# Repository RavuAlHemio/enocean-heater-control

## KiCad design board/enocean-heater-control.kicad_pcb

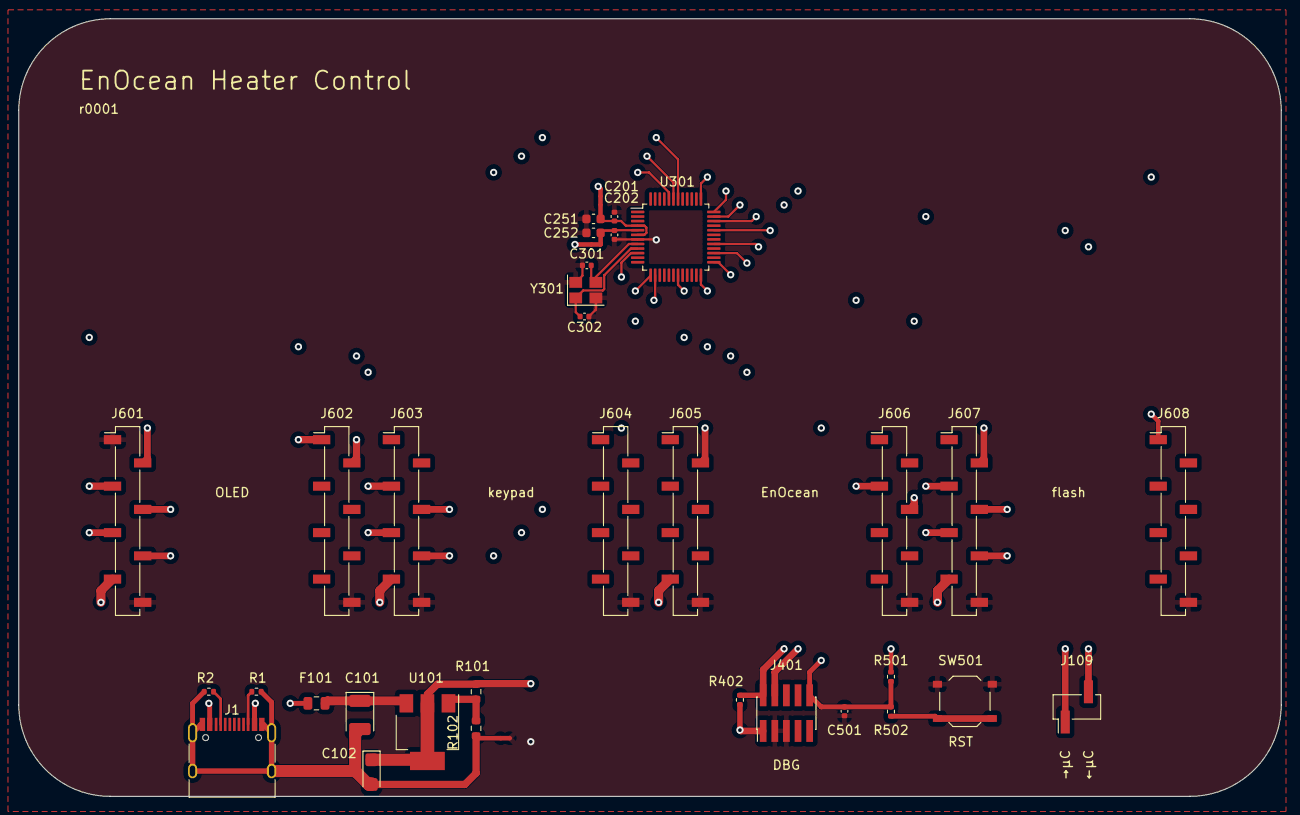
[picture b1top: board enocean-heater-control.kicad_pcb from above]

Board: 4 copper layers, 138.0 x 85.0 mm, 35 parts (0 on the bottom side), 29 nets.

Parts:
C101: 100µF; CP_EIA-3528-21_Kemet-B
C102: 10µF; CP_EIA-3216-18_Kemet-A
C201, C202, C501: 100nF; C_0402_1005Metric
C251: 4.7µF; C_0603_1608Metric
C252: 1µF; C_0603_1608Metric
C301, C302: 20pF; C_0402_1005Metric
F101: 500mA; Fuse_0805_2012Metric
J1: USB_C_Receptacle_PowerOnly_6P; USB_C_Receptacle_HRO_TYPE-C-31-M-12
J109: Conn_01x02; PinHeader_1x02_P2.54mm_Vertical_SMD_Pin1Left
J401: DBG; PinHeader_2x05_P1.27mm_Vertical_SMD
J601, J602, J603, J604, J605, J606, J607, J608: Conn_01x08; PinSocket_1x08_P2.54mm_Vertical_SMD_Pin1Left
NT101, NT201, NT202: NetTie_2; NetTie-2_SMD_Pad0.5mm
R1, R2: 5.1kΩ; R_0402_1005Metric
R101: 330Ω; R_0603_1608Metric
R102: 560Ω; R_0603_1608Metric
R402: 100kΩ; R_0402_1005Metric
R501: 2.2kΩ; R_0402_1005Metric
R502: 330Ω; R_0402_1005Metric
SW501: RST; SW_Push_1P1T_XKB_TS-1187A
U101: LM317AEMP; SOT-223-3_TabPin2
U301: STM32G0B0KETx; LQFP-48_7x7mm_P0.5mm
Y301: 16MHz; Crystal_SMD_3225-4Pin_3.2x2.5mm

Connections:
/+3.3V: C102.1, J401.1, J601.7, J603.7, J605.7, J607.7, NT201.2, NT202.1, R101.1, R402.1, R501.2, U101.2 (VO)
/CIPO: J601.5, J603.5, J607.5, U301.43 (PB4)
/COPI: J601.6, J603.6, J607.6, U301.44 (PB5)
/ENO_C2P: J606.4, U301.13 (PA2)
/ENO_P2C: J606.3, U301.14 (PA3)
/FLASH_~CS: J607.3, U301.34 (PA12/PA10)
/FLASH_~WP: J608.1, U301.37 (PA15)
/GND: C201.2, C202.2, C251.2, C252.2, C301.2, C302.1, C501.1, J401.3, J401.5, J601.1, J601.8, J602.8, J603.8, J604.8, J605.8, J606.8, J607.8, J608.8, NT101.2, SW501.1, U301.7 (VSS), Y301.2, Y301.4
/KPAD_~CS: J603.3, U301.27 (PB15)
/Microcontroller/Clock/MCU_OSC_IN: C301.1, U301.8 (PF0), Y301.3
/Microcontroller/Clock/MCU_OSC_OUT: C302.2, U301.9 (PF1), Y301.1
/Microcontroller/DBG_UART_MCURX: J109.1, U301.32 (PA10/NC)
/Microcontroller/DBG_UART_MCUTX: J109.2, U301.29 (PA9/NC)
/Microcontroller/Debug/SWCLK: J401.4, U301.36 (PA14)
/Microcontroller/Debug/SWDIO: J401.2, R402.2, U301.35 (PA13)
/Microcontroller/VDD: C201.1, C251.1, NT201.1, U301.4 (VBAT), U301.6 (VDD)
/Microcontroller/VREF+: C202.1, C252.1, NT202.2, U301.5 (VREF+)
/OLED_D_~C: J602.1, U301.24 (PB12)
/OLED_EN: J602.2, U301.25 (PB13)
/OLED_~CS: J601.3, U301.19 (PB0)
/Power Supply/GND_{USB}: C101.2, C102.2, J1.A1 (GND), J1.A12 (GND), J1.B1 (GND), J1.B12 (GND), J1.S1 (SHIELD), NT101.1, R1.2, R2.2, R102.2
/Power Supply/V_{USB}: F101.1, J1.A4 (VBUS), J1.A9 (VBUS), J1.B4 (VBUS), J1.B9 (VBUS)
/SCK: J601.4, J603.4, J607.4, U301.42 (PB3)
/~RST: C501.2, J401.10, J601.2, J605.2, J607.2, R501.1, R502.1, U301.10 (NRST)
unnamed: J1.A5 (CC1), R2.1
unnamed: J1.B5 (CC2), R1.1
unnamed: R502.2, SW501.2
unnamed: R101.2, R102.1, U101.1 (ADJ)
unnamed: C101.1, F101.2, U101.3 (VI)

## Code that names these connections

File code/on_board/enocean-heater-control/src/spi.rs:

use stm32g0b0::Peripherals;
use stm32g0b0::spi1::cr1::BR_A;


pub trait Spi {
    fn enable_clocks(&self, peripherals: &Peripherals);
    fn set_up_pins(&self, peripherals: &Peripherals);
    fn get_register_block<'a>(&self, peripherals: &'a Peripherals) -> &'a stm32g0b0::spi1::RegisterBlock;

    fn set_up(&self, peripherals: &Peripherals, clock_divider: BR_A) {
        self.enable_clocks(peripherals);
        self.set_up_pins(peripherals);

        let spi = self.get_register_block(peripherals);

        // disable SPI (and I2S, to ensure that no conflict with SPI arises)
        spi.cr1.modify(|_, w| w
            .spe().clear_bit()
        );
        spi.i2scfgr.modify(|_, w| w
            .i2se().clear_bit()
        );

        // set up SPI
        spi.cr1.modify(|_, w| w
            .cpha().clear_bit() // sample at first clock edge (in our case: 0 -> 1)
            .cpol().clear_bit() // clock to 0 when idle
            .mstr().set_bit() // enable master mode
            .lsbfirst().clear_bit() // transmit MSB first
            .ssi().clear_bit() // no internal slave select
            .ssm().set_bit() // software slave management (we select chips manually)
            .rxonly().clear_bit() // send and receive
            .crcen().clear_bit() // no hardware CRC calculation
            .bidimode().clear_bit() // no bidirectional mode; use CIPO and COPI pins
            .br().variant(clock_divider)
        );
        spi.cr2.modify(|_, w| w
            .rxdmaen().clear_bit() // don't use DMA for receive buffer
            .txdmaen().clear_bit() // don't use DMA for transmit buffer
            .nssp().clear_bit() // no ~{CS} pulse
            .frf().clear_bit() // Motorola mode (keep ~{CS} down for whole transfer instead of pulsing before transfer; see ARM manual "ddi0194")
            .errie().clear_bit() // disable interrupt on error
            .rxneie().clear_bit() // disable interrupt on Receive Buffer Not Empty
            .txeie().clear_bit() // disable interrupt on Transmit Buffer Empty
            .ds().bits8() // 8 bits of data per transfer
        );

        // alright, turn on the SPI
        spi.cr1.modify(|_, w| w
            .spe().set_bit()
        );
    }

    /// Sends data from the buffer and writes the responses into the buffer.
    fn exchange_data(&self, peripherals: &Peripherals, bytes: &mut [u8]) {
        let spi = self.get_register_block(peripherals);

        while spi.sr.read().txe().bit_is_clear() {
            // previous byte is still being sent
        }

        for b in bytes {
            // move byte to transmission register
            spi.dr.write(|w| w
                .dr().variant((*b).into())
            );

            // wait for it to be transmitted
            while spi.sr.read().txe().bit_is_clear() {
            }

            // wait for a byte to be received
            while spi.sr.read().rxne().bit_is_clear() {
            }

            // read it
            *b = (spi.dr.read().dr().bits() & 0xFF) as u8;
        }

        // wait for transmission to complete fully
        while spi.sr.read().bsy().bit_is_set() {
        }
    }
}


/// SPI1 with default pins (PB5=COPI, PB4=CIPO, PB3=SCK)
pub struct Spi1;
impl Spi for Spi1 {
    fn enable_clocks(&self, peripherals: &Peripherals) {
        // give clock to GPIOB because we are using its pins
        peripherals.RCC.iopenr.modify(|_, w| w
            .gpioben().set_bit()
        );
        // give clock to SPI1
        peripherals.RCC.apbenr2.modify(|_, w| w
            .spi1en().set_bit()
        );
    }

    fn set_up_pins(&self, peripherals: &Peripherals) {
        // hand over PB3, PB4 and PB5 to SPI1
        peripherals.GPIOB.moder.modify(|_, w| w
            .moder3().alt_func()
            .moder4().alt_func()
            .moder5().alt_func()
        );
        peripherals.GPIOA.afrl.modify(|_, w| w
            .afsel3().alt_func0()
            .afsel4().alt_func0()
            .afsel5().alt_func0()
        );
    }

    fn get_register_block<'a>(&self, peripherals: &'a Peripherals) -> &'a stm32g0b0::spi1::RegisterBlock {
        &peripherals.SPI1
    }
}

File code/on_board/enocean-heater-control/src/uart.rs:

use stm32g0b0::Peripherals;

use crate::setup::SYSTEM_CLOCK_SPEED;


pub trait Uart {
    fn enable_clocks(&self, peripherals: &Peripherals);
    fn set_up_pins(&self, peripherals: &Peripherals);
    fn get_register_block<'a>(&self, peripherals: &'a Peripherals) -> &'a stm32g0b0::usart1::RegisterBlock;

    fn set_up(&self, peripherals: &Peripherals, baud_rate: u32) {
        self.enable_clocks(peripherals);
        self.set_up_pins(peripherals);

        let usart = self.get_register_block(peripherals);

        // set up USART as UART (without FIFO mode)
        usart.cr1_fifo_disabled().modify(|_, w| w
            .ue().clear_bit() // disable USART1
            .uesm().clear_bit() // disable USART1 in low-power mode
            .re().clear_bit() // disable receiver
            .te().set_bit() // enable transmitter
            .idleie().clear_bit() // disable interrupt on IDLE
            .rxneie().clear_bit() // disable interrupt on RX [register] Not Empty
            .tcie().clear_bit() // disable interrupt on Transmission Complete
            .txeie().clear_bit() // disable interrupt on TX [register] Empty
            .peie().clear_bit() // disable interrupt on Parity Error
            .ps().clear_bit() // Even Parity (doesn't matter, we are disabling it anyway)
            .pce().clear_bit() // disable parity
            .wake().clear_bit() // wakeup from Mute mode on idle line (unused anyway)
            .m0().clear_bit() // 1 start bit, 8 data bits (part 1)
            .m1().clear_bit() // 1 start bit, 8 data bits (part 2)
            .mme().clear_bit() // disable Mute mode
            .cmie().clear_bit() // disable interrupt on character match
            .over8().clear_bit() // oversample by 16
            // keep DEDT and DEAT unchanged
            .rtoie().clear_bit() // disable interrupt on Receiver Timeout
            .eobie().clear_bit() // disable interrupt on End Of Block
            .fifoen().clear_bit() // disable FIFO mode
        );
        usart.cr2.modify(|_, w| w
            .slven().clear_bit() // disable synchronous slave mode
            .lbdie().clear_bit() // disable interrupt on LIN Break Detection
            .clken().clear_bit() // disable SCLK pin
            .stop().one() // one stop bit
            .linen().clear_bit() // disable LIN mode
            .swap().clear_bit() // don't swap Rx and Tx
            .rxinv().clear_bit() // don't assume Rx is inverted
            .txinv().clear_bit() // don't invert Tx
            .datainv().clear_bit() // don't invert data
            .msbfirst().clear_bit() // send LSB first (as expected by RS232)
            .abren().clear_bit() // don't do automatic baud rate detection
            .rtoen().clear_bit() // don't do receiver timeout
        );
        usart.cr3.modify(|_, w| w
            .eie().clear_bit() // disable error interrupt
            .iren().clear_bit() // disable IrDA mode
            .hdsel().clear_bit() // full duplex (if you actually do half-duplex, we cannot be friends)
            .nack().clear_bit() // no smartcard NACK
            .scen().clear_bit() // disable smartcard mode
            .dmar().clear_bit() // disable receiver DMA
            .dmat().clear_bit() // disable transmitter DMA
            .rtse().clear_bit() // disable RTS (ready-to-receive) flow control
            .ctse().clear_bit() // disable CTS (clear-to-send) flow control
            .ctsie().clear_bit() // disable interrupt on clear-to-send
            .onebit().clear_bit() // use 3-bit sample mode
            .ovrdis().set_bit() // ignore receive buffer overruns
            .dem().clear_bit() // disable external transceiver control
            .wufie().clear_bit() // disable interrupt on wake-up from low power state
            .txftie().clear_bit() // disable interrupt on TX FIFO threshold reached
            .tcbgtie().clear_bit() // disable interrupt on transmission complete before guard time reached
            .rxftie().clear_bit() // disable interrupt on RX FIFO threshold reached
        );

        // baud rate calculation
        // USARTDIV = usart_ker_ckpres / baud
        // where usart_ker_ckpres = usart_ker_ck prescaled by value in PRESC
        // assuming usart_ker_ck = usart_pclk = sysclk = 64 MHz
        // and desired baud rate = 115200 bps (bps = Hz)
        // => USARTDIV = 555
        let baud_divider = SYSTEM_CLOCK_SPEED / baud_rate;
        debug_assert!(baud_divider <= 0xFFFF);
        usart.brr.modify(|_, w| w
            .brr().variant((baud_divider & 0xFFFF) as u16)
        );

        // alright, turn on the UART
        usart.cr1_fifo_disabled().modify(|_, w| w
            .ue().set_bit() // USART enable
        );
    }

    fn send(&self, peripherals: &Peripherals, bytes: &[u8]) {
        let usart = self.get_register_block(peripherals);

        while usart.isr_fifo_disabled().read().txe().bit_is_clear() {
            // previous byte is still being sent
        }

        for &b in bytes {
            // move byte to transmission register
            usart.tdr.write(|w| w
                .tdr().variant(b.into())
            );

            // wait for it to be transmitted
            while usart.isr_fifo_disabled().read().txe().bit_is_clear() {
            }
        }

        // wait for transmission to complete fully
        while usart.isr_fifo_disabled().read().tc().bit_is_clear() {
        }
    }
}


/// UART on USART1 with default pins (PA9=Tx, PA10=Rx)
pub struct Uart1;
impl Uart for Uart1 {
    fn enable_clocks(&self, peripherals: &Peripherals) {
        // give clock to GPIOA because we are using its pins
        peripherals.RCC.iopenr.modify(|_, w| w
            .gpioaen().set_bit()
        );
        // give clock to USART1
        peripherals.RCC.apbenr2.modify(|_, w| w
            .usart1en().set_bit()
        );
    }

    fn set_up_pins(&self, peripherals: &Peripherals) {
        // hand over PA9 and PA10 to USART1
        peripherals.GPIOA.moder.modify(|_, w| w
            .moder9().alt_func()
            .moder10().alt_func()
        );
        peripherals.GPIOA.afrh.modify(|_, w| w
            .afsel9().alt_func1()
            .afsel10().alt_func1()
        );
    }

    fn get_register_block<'a>(&self, peripherals: &'a Peripherals) -> &'a stm32g0b0::usart1::RegisterBlock {
        &peripherals.USART1
    }
}


/// UART on USART2 with default pins (PA2=Tx, PA3=Rx)
pub struct Uart2;
impl Uart for Uart2 {
    fn enable_clocks(&self, peripherals: &Peripherals) {
        // give clock to GPIOA because we are using its pins
        peripherals.RCC.iopenr.modify(|_, w| w
            .gpioaen().set_bit()
        );
        // give clock to USART2
        peripherals.RCC.apbenr1.modify(|_, w| w
            .usart2en().set_bit()
        );
    }

    fn set_up_pins(&self, peripherals: &Peripherals) {
        // hand over PA2 and PA3 to USART2
        peripherals.GPIOA.moder.modify(|_, w| w
            .moder2().alt_func()
            .moder3().alt_func()
        );
        peripherals.GPIOA.afrl.modify(|_, w| w
            .afsel2().alt_func1()
            .afsel3().alt_func1()
        );
    }

    fn get_register_block<'a>(&self, peripherals: &'a Peripherals) -> &'a stm32g0b0::usart1::RegisterBlock {
        &peripherals.USART2
    }
}

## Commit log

2023-11-08 initial commit (board)
2023-11-14 redo board with STM32G0B0CET
2023-11-14 initialization code
